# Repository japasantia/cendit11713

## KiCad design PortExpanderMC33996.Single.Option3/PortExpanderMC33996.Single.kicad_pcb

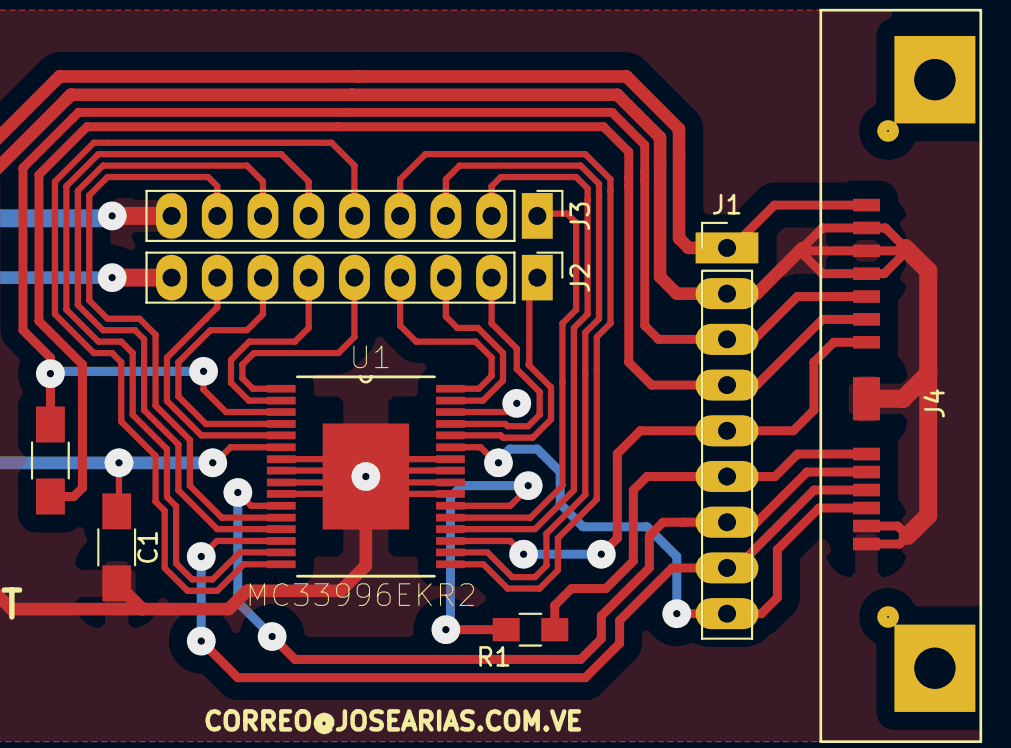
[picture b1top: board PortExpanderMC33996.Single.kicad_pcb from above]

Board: 2 copper layers, 8 parts (0 on the bottom side), 26 nets.

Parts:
C1: 0.1uF/30V; C_1206_HandSoldering
C2: 0.1uF/10V; C_1206_HandSoldering
J1: DEBUG_CON_9P
J2, J3: VIKING_CON_9P; VIKING_HEADER_9P
J4: SATA_CON_14P; SLIMLINE_SATA_PLUG_7P_6P
R1: 1k; R_0805_HandSoldering
U1: MC33996EKR2; MC33996-SOIC32

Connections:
+24.0V: C1.1, J1.1, J2.9, J4.13, U1.6
//CS: J1.8, J4.4, U1.14
//RESET: J1.9, J4.3, U1.27
/MISO: J1.6, J4.6, R1.1
/MOSI: J1.5, J4.7, U1.19
/SCLK: J1.7, J4.5, U1.11
/VKX0: J2.5, U1.1
/VKX1: J2.6, U1.2
/VKX2: J2.7, U1.4
/VKX3: J2.8, U1.5
/VKX4: J3.8, U1.12
/VKX5: J3.7, U1.13
/VKX6: J3.6, U1.15
/VKX7: J3.5, U1.16
/VKX8: J3.4, U1.17
/VKX9: J3.3, U1.18
/VKX10: J3.2, U1.20
/VKX11: J3.1, U1.21
/VKX12: J2.1, U1.28
/VKX13: J2.2, U1.29
/VKX14: J2.3, U1.31
/VKX15: J2.4, U1.32
GND: C2.2, J1.4, J4.8
GNDPWR: C1.2, J1.2, J3.9, J4.1, J4.2, J4.10, J4.11, J4.12, J4.14, U1.7, U1.8, U1.9, U1.10, U1.23, U1.24, U1.25, U1.26, U1.33
unnamed: R1.2, U1.22
VDD: C2.1, J1.3, J4.9, U1.3

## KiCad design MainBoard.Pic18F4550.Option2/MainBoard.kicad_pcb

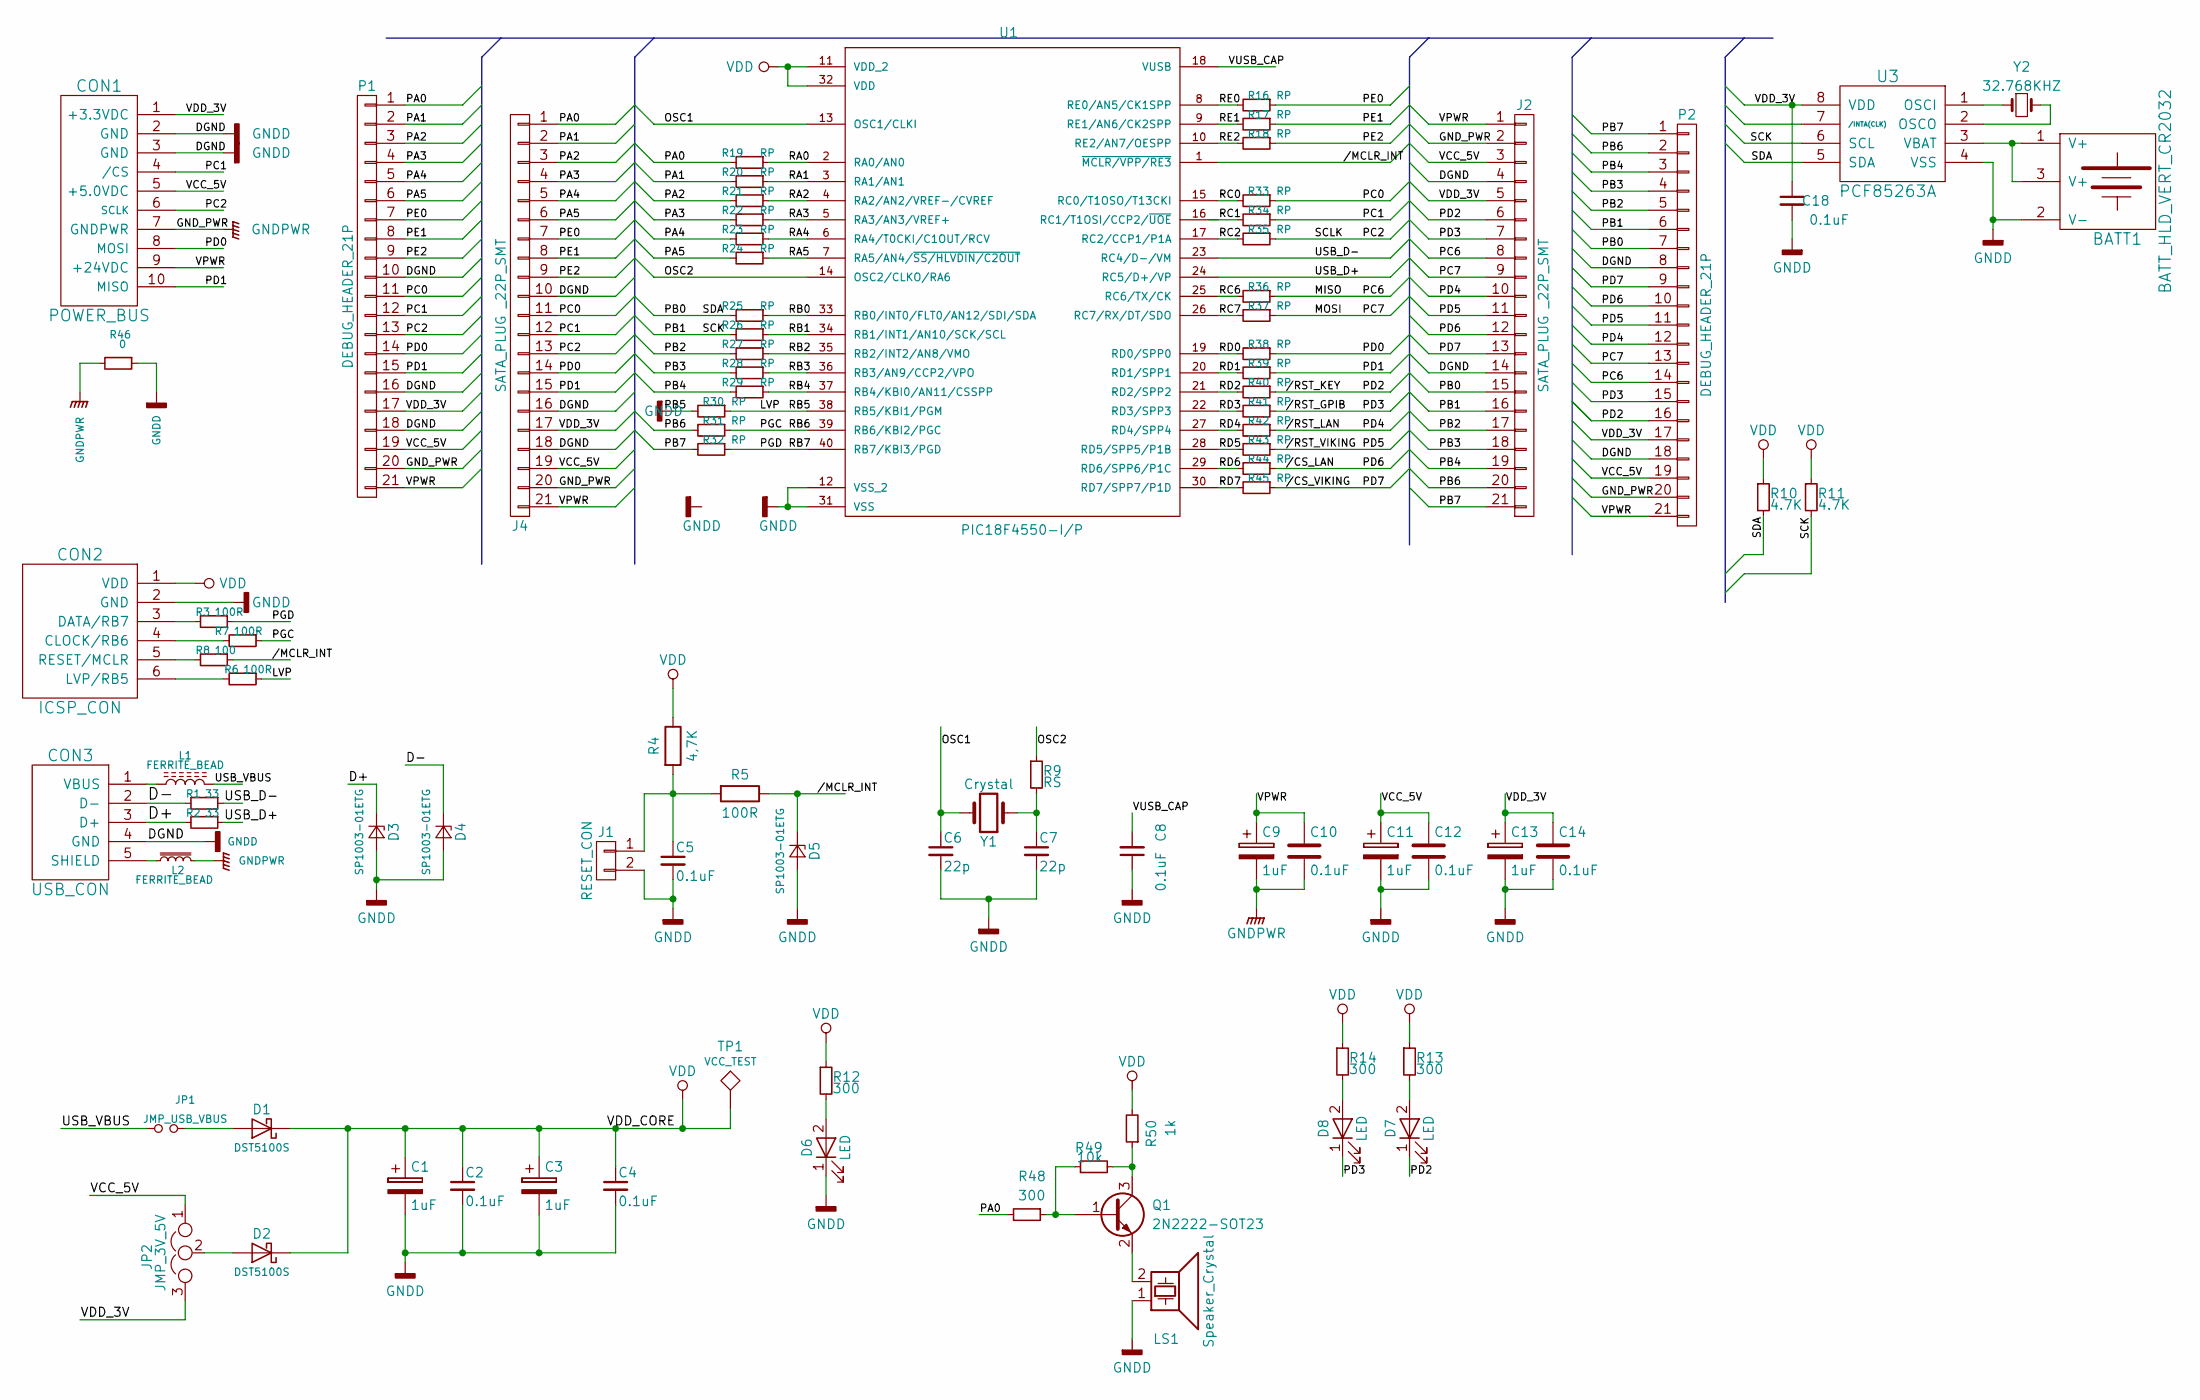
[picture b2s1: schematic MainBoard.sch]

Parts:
BATT1: BATT_HLD_VERT_CR2032; BATTERY_HOLDER_VERT_CR2032
C1, C3, C9, C11, C13: 1uF; C_1206_HandSoldering
C2, C4, C5, C10, C12, C14, C18: 0.1uF; C_0805_HandSoldering
C6, C7: 22p; C_0805_HandSoldering
C8: 0.1uF; C_1206_HandSoldering
CON1: POWER_BUS; Pin_Header_Straight_2x05_Pitch2.54mm
CON2: ICSP_CON; Pin_Header_Straight_2x03
CON3: USB_CON; USB_SMT_B
D1, D2: DST5100S; DST5100S-TO-277B
D3, D4, D5: SP1003-01ETG
D6, D7, D8: LED; LED_0805
J1: RESET_CON; Pin_Header_Straight_1x02_Pitch2.54mm
J2, J4: SATA_PLUG _22P_SMT; SATA_PLUG_22P_SMT
JP1: JMP_USB_VBUS; Pin_Header_Straight_1x02_Pitch2.54mm
JP2: JMP_3V_5V; Pin_Header_Straight_1x03
L1, L2: FERRITE_BEAD; L_Axial_L5.3mm_D2.2mm_P2.54mm_Vertical_Vishay_IM-1
LS1: Speaker_Crystal; MagneticBuzzer_Kingstate_KCG0601
P1, P2: DEBUG_HEADER_21P; DEBUG_PIN_HEADER_21P
Q1: 2N2222-SOT23; SOT-23_Handsoldering
R1, R2: 33; R_0603_HandSoldering
R3, R5, R6, R7: 100R; R_0805_HandSoldering
R4: 4,7K; R_0805_HandSoldering
R8: 100; R_0805_HandSoldering
R9: RS; R_0805_HandSoldering
R10, R11: 4.7K; R_0805_HandSoldering
R12, R13, R14: 300; R_0805_HandSoldering
R16, R17, R18, R19, R20, R21, R22, R23, R24, R25, R26, R27, R28, R29, R30, R31, R32, R33, R34, R35, R36, R37, R38, R39, R40, R41, R42, R43, R44, R45: RP; R_0805_HandSoldering
R46: 0; R_0805_HandSoldering
R48: 300; R_0603_HandSoldering
R49: 10k; R_0603_HandSoldering
R50: 1k; R_0603_HandSoldering
TP1: VCC_TEST
U1: PIC18F4550-I/P; PIC18F4550-PDIP
U3: PCF85263A; PCF85263A_SO8
Y1: Crystal; Crystal_SMD_HC49-SD
Y2: 32.768KHZ; Crystal_C26-LF_d2.1mm_l6.5mm_Vertical

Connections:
//CS_LAN: J2.12, P2.10, R44.1
//CS_VIKING: J2.13, P2.9, R45.1
//MCLR_INT: D5.1 (K), R5.1, R8.1, U1.1 (~MCLR/VPP/RE3)
//RST_GPIB: D8.1 (K), J2.7, P2.15, R41.1
//RST_KEY: D7.1 (K), J2.6, P2.16, R40.1
//RST_LAN: J2.10, P2.12, R42.1
//RST_VIKING: J2.11, P2.11, R43.1
/D+: CON3.3 (D+), D3.1 (K), R2.2
/D-: CON3.2 (D-), D4.1 (K), R1.2
/LVP: R6.1, R30.1, U1.38 (RB5/KBI1/PGM)
/MISO: J2.8, P2.14, R36.1
/MOSI: J2.9, P2.13, R37.1
/OSC1: C6.1, U1.13 (OSC1/CLKI), Y1.2
/OSC2: R9.1, U1.14 (OSC2/CLKO/RA6)
/PA0: J4.1, P1.1, R19.2, R48.2
/PA1: J4.2, P1.2, R20.2
/PA2: J4.3, P1.3, R21.2
/PA3: J4.4, P1.4, R22.2
/PA4: J4.5, P1.5, R23.2
/PA5: J4.6, P1.6, R24.2
/PB0: J2.15, P2.7, R10.2, R25.2, U3.5 (SDA)
/PB1: J2.16, P2.6, R11.2, R26.2, U3.6 (SCL)
/PB2: J2.17, P2.5, R27.2
/PB3: J2.18, P2.4, R28.2
/PB4: J2.19, P2.3, R29.2
/PB6: J2.20, P2.2, R31.2
/PB7: J2.21, P2.1, R32.2
/PC0: J4.11, P1.11, R33.1
/PC1: CON1.4 (/CS), J4.12, P1.12, R34.1
/PC2: CON1.6 (SCLK), J4.13, P1.13, R35.1
/PD0: CON1.8 (MOSI), J4.14, P1.14, R38.1
/PD1: CON1.10 (MISO), J4.15, P1.15, R39.1
/PE0: J4.7, P1.7, R16.1
/PE1: J4.8, P1.8, R17.1
/PE2: J4.9, P1.9, R18.1
/PGC: R7.1, R31.1, U1.39 (RB6/KBI2/PGC)
/PGD: R3.1, R32.1, U1.40 (RB7/KBI3/PGD)
/RA0: R19.1, U1.2 (RA0/AN0)
/RA1: R20.1, U1.3 (RA1/AN1)
/RA2: R21.1, U1.4 (RA2/AN2/VREF-/CVREF)
/RA3: R22.1, U1.5 (RA3/AN3/VREF+)
/RA4: R23.1, U1.6 (RA4/T0CKI/C1OUT/RCV)
/RA5: R24.1, U1.7 (RA5/AN4/~SS/HLVDIN/C2OUT)
/RB0: R25.1, U1.33 (RB0/INT0/FLT0/AN12/SDI/SDA)
/RB1: R26.1, U1.34 (RB1/INT1/AN10/SCK/SCL)
/RB2: R27.1, U1.35 (RB2/INT2/AN8/VMO)
/RB3: R28.1, U1.36 (RB3/AN9/CCP2/VPO)
/RB4: R29.1, U1.37 (RB4/KBI0/AN11/CSSPP)
/RC0: R33.2, U1.15 (RC0/T1OSO/T13CKI)
/RC1: R34.2, U1.16 (RC1/T1OSI/CCP2/~UOE)
/RC2: R35.2, U1.17 (RC2/CCP1/P1A)
/RC6: R36.2, U1.25 (RC6/TX/CK)
/RC7: R37.2, U1.26 (RC7/RX/DT/SDO)
/RD0: R38.2, U1.19 (RD0/SPP0)
/RD1: R39.2, U1.20 (RD1/SPP1)
/RD2: R40.2, U1.21 (RD2/SPP2)
/RD3: R41.2, U1.22 (RD3/SPP3)
/RD4: R42.2, U1.27 (RD4/SPP4)
/RD5: R43.2, U1.28 (RD5/SPP5/P1B)
/RD6: R44.2, U1.29 (RD6/SPP6/P1C)
/RD7: R45.2, U1.30 (RD7/SPP7/P1D)
/RE0: R16.2, U1.8 (RE0/AN5/CK1SPP)
/RE1: R17.2, U1.9 (RE1/AN6/CK2SPP)
/RE2: R18.2, U1.10 (RE2/AN7/OESPP)
/USB_D+: R2.1, U1.24 (RC5/D+/VP)
/USB_D-: R1.1, U1.23 (RC4/D-/VM)
/USB_VBUS: JP1.1, L1.2
/VCC_5V: C11.1, C12.1, CON1.5 (+5.0VDC), J2.3, J4.19, JP2.1, P1.19, P2.19
/VDD_3V: C13.1, C14.1, C18.1, CON1.1 (+3.3VDC), J2.5, J4.17, JP2.3, P1.17, P2.17, U3.8 (VDD)
/VPWR: C9.1, C10.1, CON1.9 (+24VDC), J2.1, J4.21, P1.21, P2.21
/VUSB_CAP: C8.2, U1.18 (VUSB)
GNDD: BATT1.2 (V-), C1.2, C2.2, C3.2, C4.2, C5.2, C6.2, C7.2, C8.1, C11.2, C12.2, C13.2, C14.2, C18.2, CON1.2 (GND), CON1.3 (GND), CON2.2 (GND), CON3.4 (GND), D3.2 (A), D4.2 (A), D5.2 (A), D6.1 (K), J1.2, J2.4, J2.14, J4.10, J4.16, J4.18, LS1.1, P1.10, P1.16, P1.18, P2.8, P2.18, R30.2, R46.1, U1.12 (VSS_2), U1.31 (VSS), U3.4 (VSS)
GNDPWR: C9.2, C10.2, CON1.7 (GNDPWR), J2.2, J4.20, L2.2, P1.20, P2.20, R46.2
unnamed: BATT1.1 (V+), BATT1.3 (V+), U3.3 (VBAT)
unnamed: C5.1, J1.1, R4.2, R5.2
unnamed: C7.1, R9.2, Y1.1
unnamed: CON2.3 (DATA/RB7), R3.2
unnamed: CON2.4 (CLOCK/RB6), R7.2
unnamed: CON2.5 (RESET/MCLR), R8.2
unnamed: CON2.6 (LVP/RB5), R6.2
unnamed: CON3.1 (VBUS), L1.1
unnamed: CON3.5 (SHIELD), L2.1
unnamed: D1.2 (A), JP1.2
unnamed: D2.2 (A), JP2.2
unnamed: D6.2 (A), R12.2
unnamed: D7.2 (A), R13.2
unnamed: D8.2 (A), R14.2
unnamed: LS1.2, Q1.2 (E)
unnamed: Q1.1 (B), R48.1, R49.1
unnamed: Q1.3 (C), R49.2, R50.1
unnamed: U3.1 (OSCI), Y2.1
unnamed: U3.2 (OSCO), Y2.2
VDD: C1.1, C2.1, C3.1, C4.1, CON2.1 (VDD), D1.1 (K), D2.1 (K), R4.1, R10.1, R11.1, R12.1, R13.1, R14.1, R50.2, TP1.1, U1.11 (VDD_2), U1.32 (VDD)

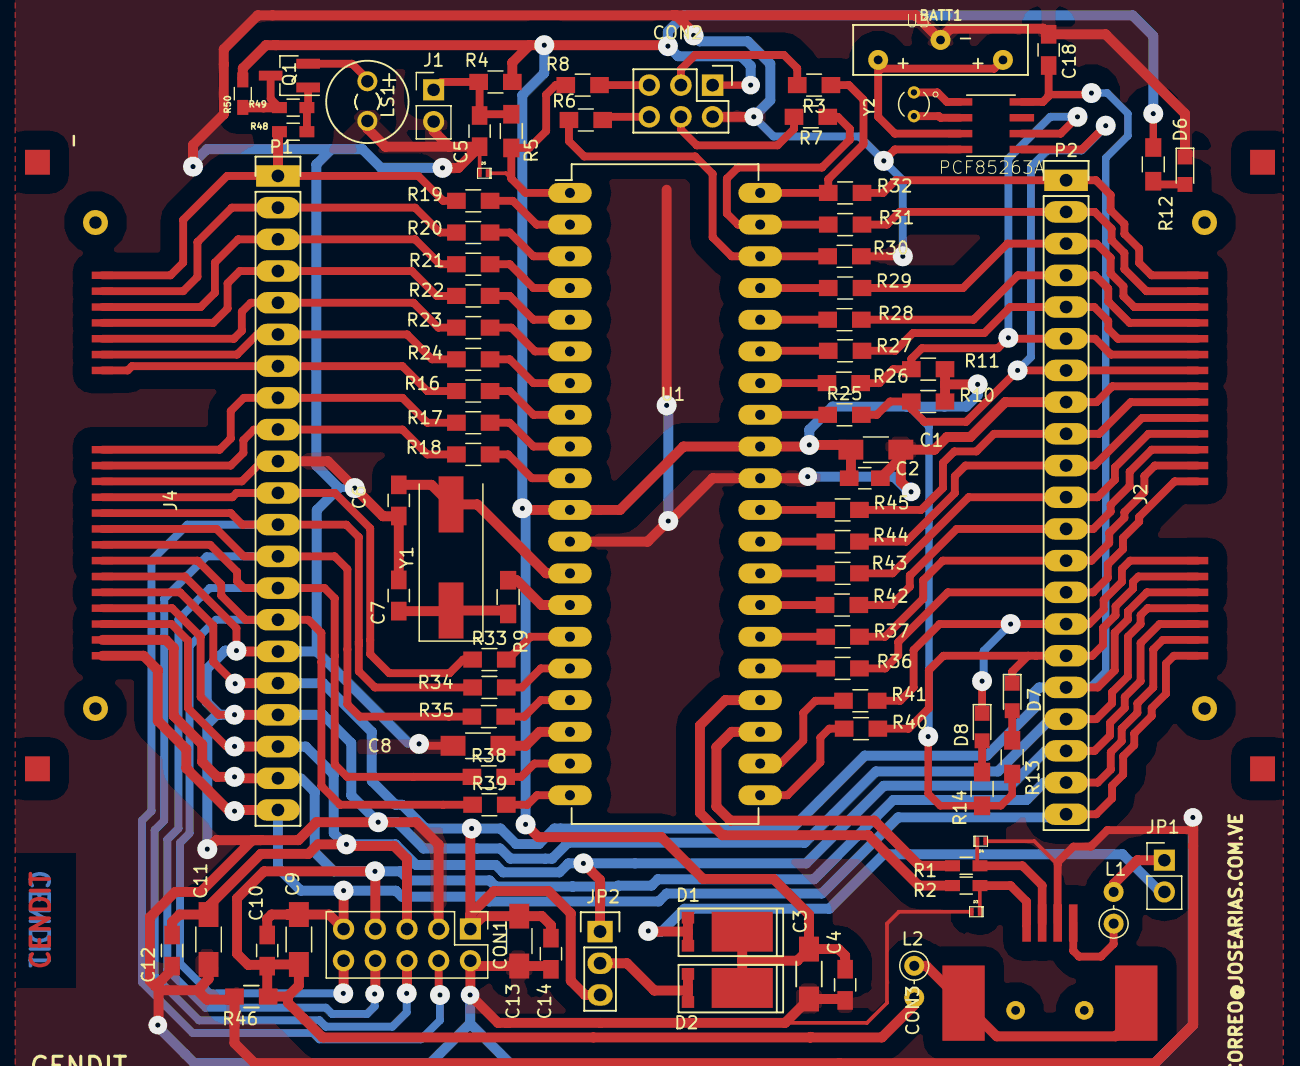
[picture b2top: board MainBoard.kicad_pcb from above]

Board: 2 copper layers, 90 parts (0 on the bottom side), 93 nets.

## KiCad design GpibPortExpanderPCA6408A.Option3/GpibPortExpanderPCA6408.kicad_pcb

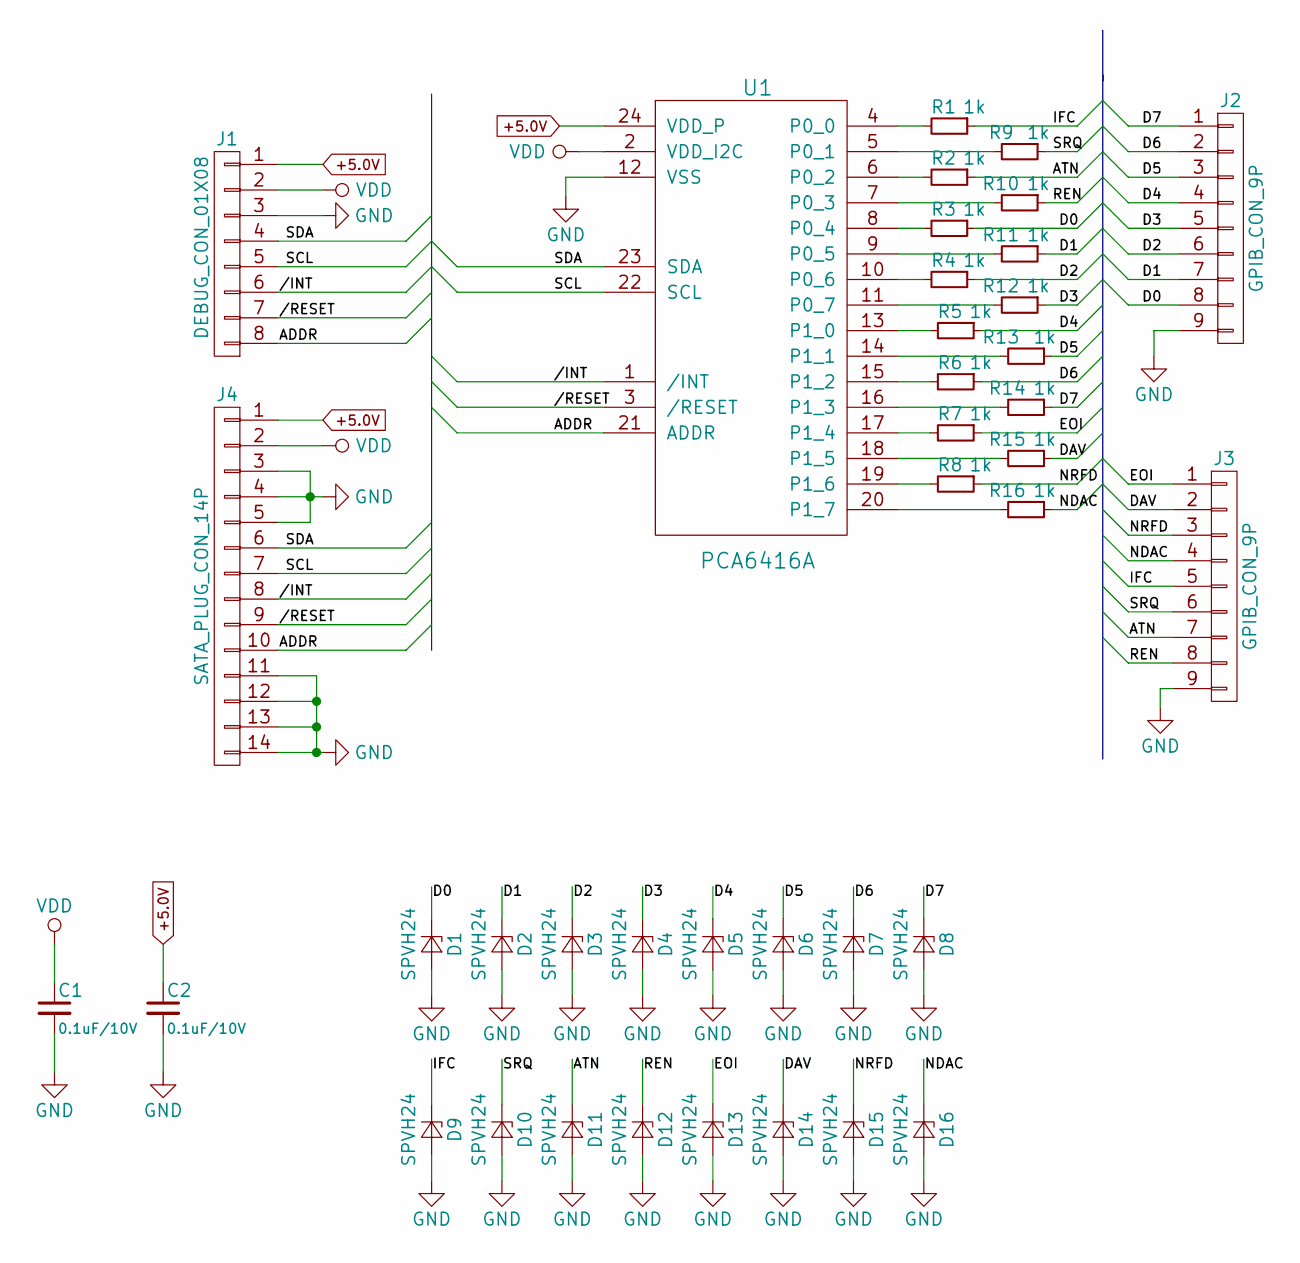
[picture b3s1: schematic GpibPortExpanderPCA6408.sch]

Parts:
C1, C2: 0.1uF/10V; C_1206_HandSoldering
D1, D2, D3, D4, D5, D6, D7, D8, D9, D10, D11, D12, D13, D14, D15, D16: SPVH24; SPHV24-SOD882
J1: DEBUG_CON_01X08; DEBUG_CON_8P
J2, J3: GPIB_CON_9P; GPIB_HEADER_9P
J4: SATA_PLUG_CON_14P; SLIMLINE_SATA_PLUG_7P_6P
R1, R2, R3, R4, R5, R6, R7, R8, R9, R10, R11, R12, R13, R14, R15, R16: 1k; R_0805_HandSoldering
U1: PCA6416A; PCA6416A-TSSOP24

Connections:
+5.0V: C2.1, J1.1, J4.1, U1.24 (VDD_P)
//INT: J1.6, J4.8, U1.1 (/INT)
//RESET: J1.7, J4.9, U1.3 (/RESET)
/ADDR: J1.8, J4.10, U1.21 (ADDR)
/ATN: D11.1 (K), J3.7, R2.1
/D0: D1.1 (K), J2.8, R3.1
/D1: D2.1 (K), J2.7, R11.1
/D2: D3.1 (K), J2.6, R4.1
/D3: D4.1 (K), J2.5, R12.1
/D4: D5.1 (K), J2.4, R5.1
/D5: D6.1 (K), J2.3, R13.1
/D6: D7.1 (K), J2.2, R6.1
/D7: D8.1 (K), J2.1, R14.1
/DAV: D14.1 (K), J3.2, R15.1
/EOI: D13.1 (K), J3.1, R7.1
/IFC: D9.1 (K), J3.5, R1.1
/NDAC: D16.1 (K), J3.4, R16.1
/NRFD: D15.1 (K), J3.3, R8.1
/REN: D12.1 (K), J3.8, R10.1
/SCL: J1.5, J4.7, U1.22 (SCL)
/SDA: J1.4, J4.6, U1.23 (SDA)
/SRQ: D10.1 (K), J3.6, R9.1
GND: C1.2, C2.2, D1.2 (A), D2.2 (A), D3.2 (A), D4.2 (A), D5.2 (A), D6.2 (A), D7.2 (A), D8.2 (A), D9.2 (A), D10.2 (A), D11.2 (A), D12.2 (A), D13.2 (A), D14.2 (A), D15.2 (A), D16.2 (A), J1.3, J2.9, J3.9, J4.3, J4.4, J4.5, J4.11, J4.12, J4.13, J4.14, U1.12 (VSS)
unnamed: R1.2, U1.4 (P0_0)
unnamed: R2.2, U1.6 (P0_2)
unnamed: R3.2, U1.8 (P0_4)
unnamed: R4.2, U1.10 (P0_6)
unnamed: R5.2, U1.13 (P1_0)
unnamed: R6.2, U1.15 (P1_2)
unnamed: R7.2, U1.17 (P1_4)
unnamed: R8.2, U1.19 (P1_6)
unnamed: R9.2, U1.5 (P0_1)
unnamed: R10.2, U1.7 (P0_3)
unnamed: R11.2, U1.9 (P0_5)
unnamed: R12.2, U1.11 (P0_7)
unnamed: R13.2, U1.14 (P1_1)
unnamed: R14.2, U1.16 (P1_3)
unnamed: R15.2, U1.18 (P1_5)
unnamed: R16.2, U1.20 (P1_7)
VDD: C1.1, J1.2, J4.2, U1.2 (VDD_I2C)

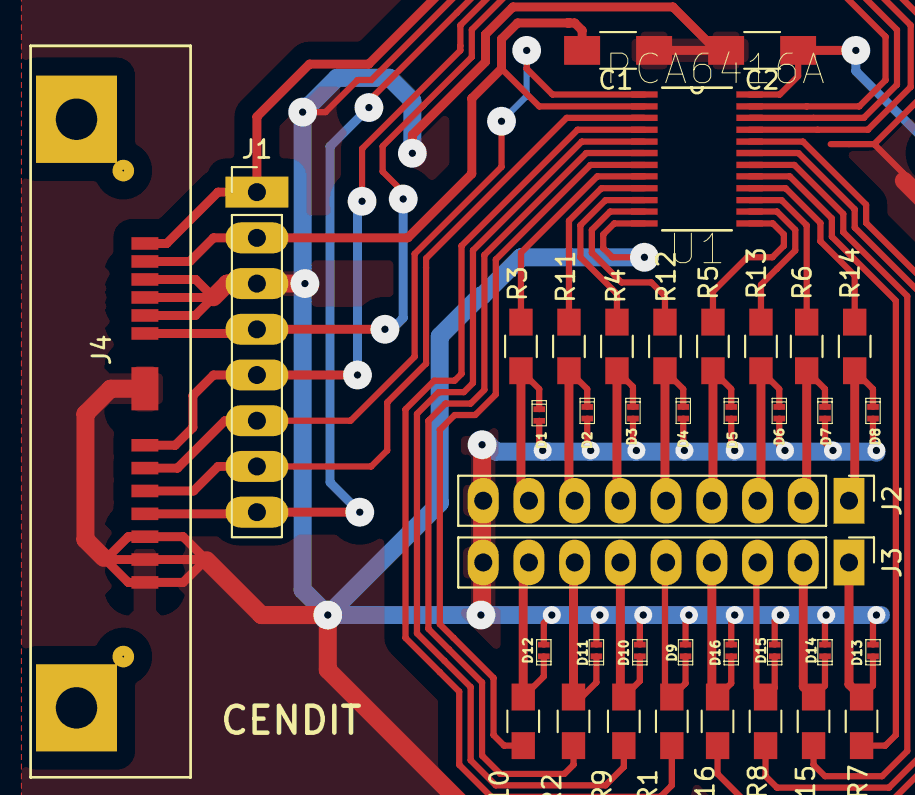
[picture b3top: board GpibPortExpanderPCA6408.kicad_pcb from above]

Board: 2 copper layers, 39 parts (0 on the bottom side), 40 nets.

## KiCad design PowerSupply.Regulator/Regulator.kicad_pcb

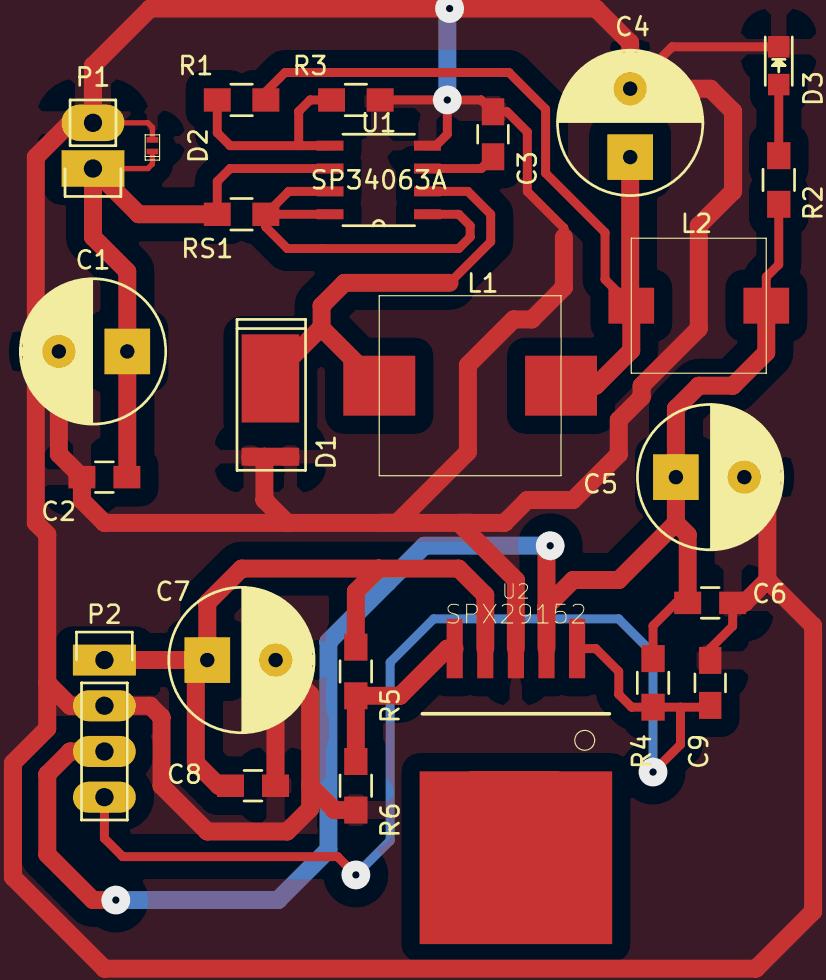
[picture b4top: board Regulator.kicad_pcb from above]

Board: 2 copper layers, 25 parts (0 on the bottom side), 12 nets.

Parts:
C1: 100uF@50V; C_Radial_D8_L13_P3.8
C2, C6, C8: 100nF; C_0805_HandSoldering
C3: 0.3nF; C_0805_HandSoldering
C4: 470uF@10V; C_Radial_D8_L13_P3.8
C5, C7: 100uF@10V; C_Radial_D8_L13_P3.8
C9: 1uF; C_0805_HandSoldering
D1: DST5100S; DST5100S-TO-277B
D2: SPHV24-01ETG; SPHV24-SOD882
D3: LED; LED_0805
L1: 220uH; INDUCTOR_LCM1060
L2: 1uH; INDUCTOR_LKS0745
P1: PWR_IN_2P; Pin_Header_Straight_1x02
P2: PWR_OUT_4P; Pin_Header_Straight_1x04
R1: 2.0k; R_0805_HandSoldering
R2: 330; R_0805_HandSoldering
R3: 1.0k; R_0805_HandSoldering
R4: 10k; R_0805_HandSoldering
R5: 4.3k; R_0805_HandSoldering
R6: 3.0k; R_0805_HandSoldering
RS1: 0.20; R_0805_HandSoldering
U1: SP34063A; SP34063AEN-L&slash_TR
U2: SPX29152; SPX29152T5-TO-263-5

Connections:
/ENABLE: C9.1, P2.4, R4.1, U2.1
GNDPWR: C1.2, C2.2, C3.2, C4.2, C5.2, C6.2, C7.2, C8.2, C9.2, D1.2, D2.2, D3.1, P1.2, P2.2, R3.1, R6.1, U1.4, U2.3
unnamed: C3.1, U1.3
unnamed: C4.1, L1.2, L2.1, R1.1
unnamed: D1.1, L1.1, U1.2
unnamed: D3.2, R2.2
unnamed: R1.2, R3.2, U1.5
unnamed: R5.1, R6.2, U2.5
unnamed: RS1.1, U1.1, U1.7, U1.8
VIN: C1.1, C2.1, D2.1, P1.1, RS1.2, U1.6
VOUT: C7.1, C8.1, P2.1, R5.2, U2.4
VREG: C5.1, C6.1, L2.2, P2.3, R2.1, R4.2, U2.2

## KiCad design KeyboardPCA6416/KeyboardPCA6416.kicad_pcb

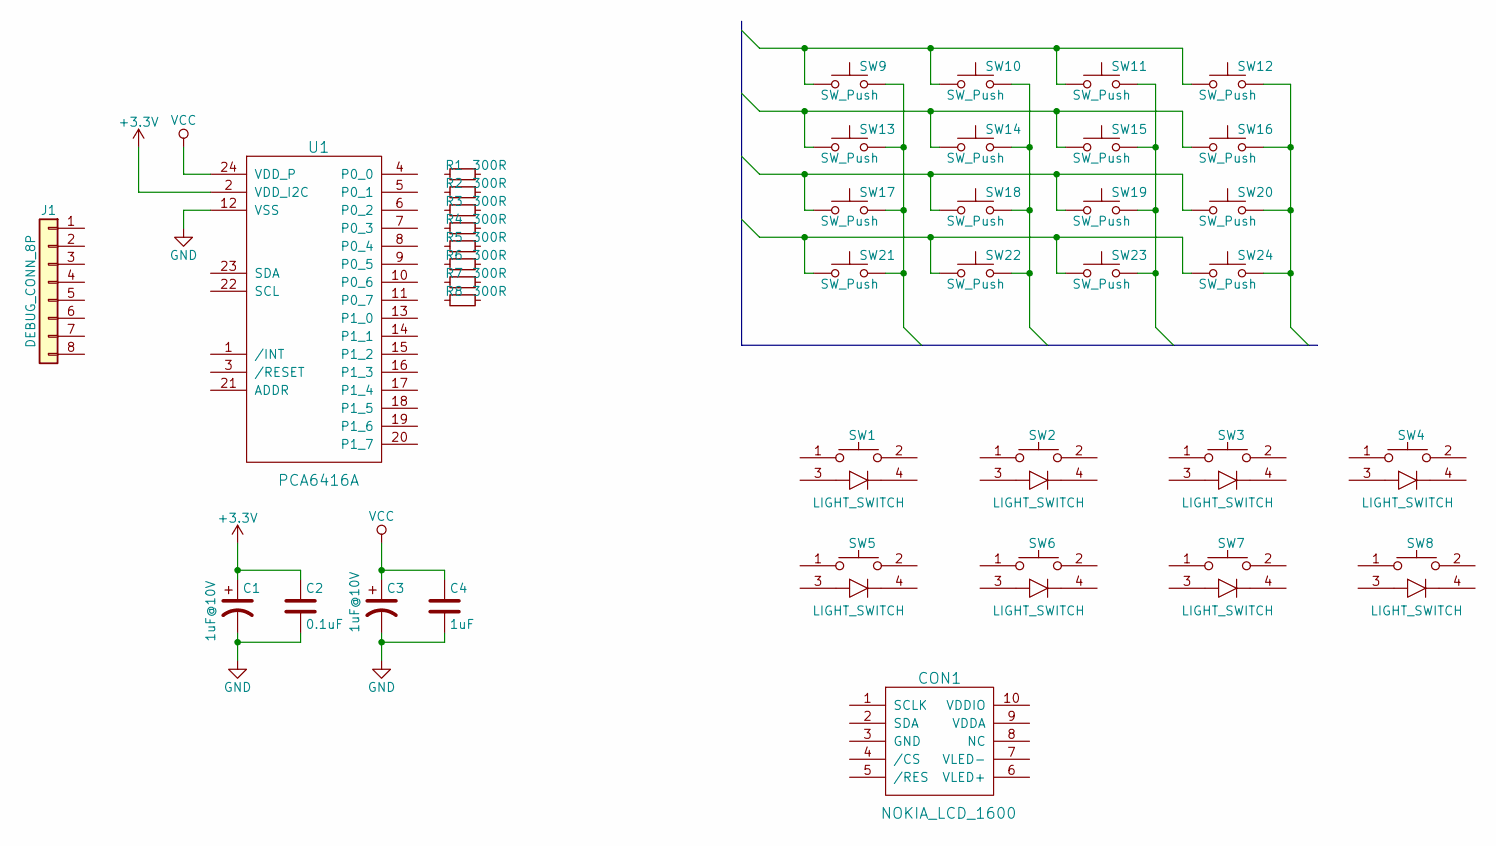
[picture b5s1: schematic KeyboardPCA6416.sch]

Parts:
C1, C3: 1uF@10V; C_0805_HandSoldering
C2: 0.1uF; C_0805_HandSoldering
C4: 1uF; C_0805_HandSoldering
CON1: NOKIA_LCD_1600; HIROSE_DF23C_10P
J1: DEBUG_CONN_8P; Pin_Header_Straight_1x08_Pitch2.54mm
R1, R2, R3, R4, R5, R6, R7, R8: 300R; R_0805_HandSoldering
SW1, SW2, SW3, SW4, SW5, SW6, SW7, SW8: LIGHT_SWITCH; LIGHT_SWITCH_THT
SW9, SW10, SW11, SW12, SW13, SW14, SW15, SW16, SW17, SW18, SW19, SW20, SW21, SW22, SW23, SW24: SW_Push; SWITCH_THT_6MM
U1: PCA6416A; PCA6416A-TSSOP24

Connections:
+3V3: C1.1, C2.1, U1.2 (VDD_I2C)
GND: C1.2, C2.2, C3.2, C4.2, U1.12 (VSS)
unnamed: SW9.1, SW10.1, SW11.1, SW12.1
unnamed: SW10.2, SW14.2, SW18.2, SW22.2
unnamed: SW11.2, SW15.2, SW19.2, SW23.2
unnamed: SW12.2, SW16.2, SW20.2, SW24.2
unnamed: SW13.1, SW14.1, SW15.1, SW16.1
unnamed: SW9.2, SW13.2, SW17.2, SW21.2
unnamed: SW17.1, SW18.1, SW19.1, SW20.1
unnamed: SW21.1, SW22.1, SW23.1, SW24.1
VCC: C3.1, C4.1, U1.24 (VDD_P)

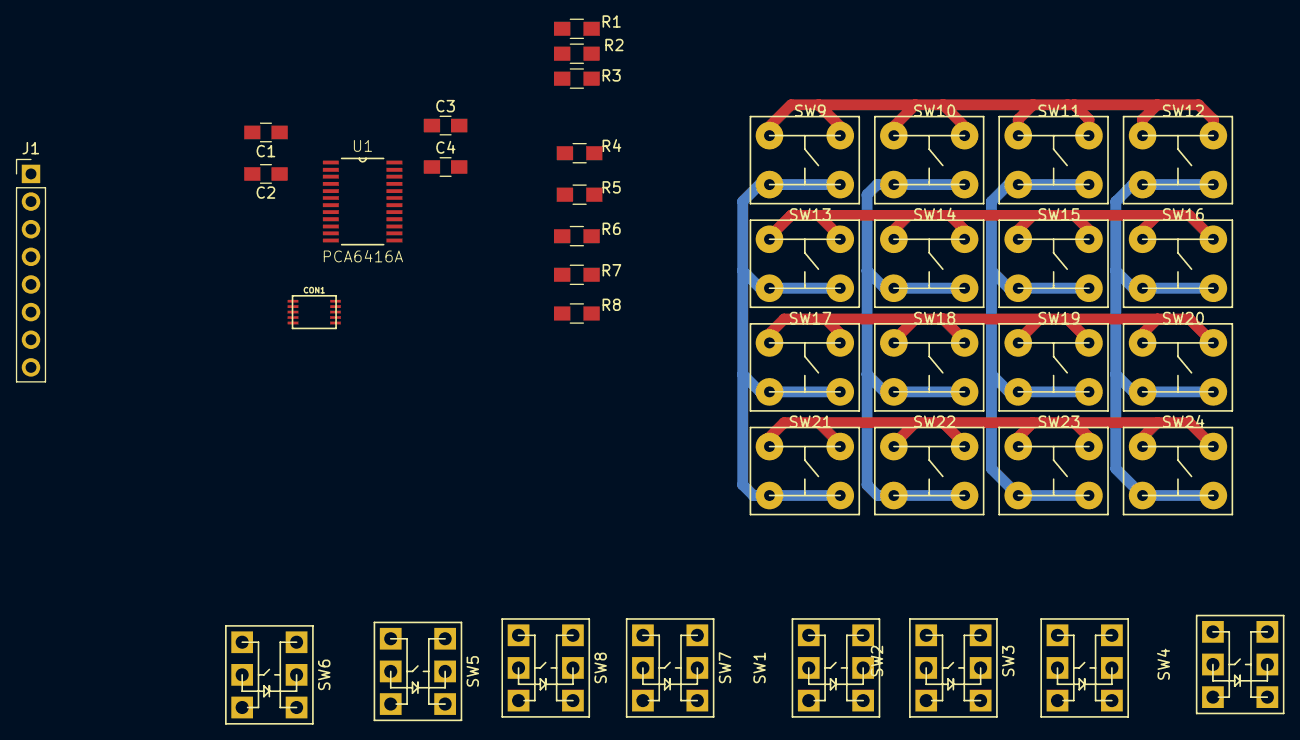
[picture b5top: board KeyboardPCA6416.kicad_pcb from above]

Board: 2 copper layers, 39 parts (0 on the bottom side), 11 nets.

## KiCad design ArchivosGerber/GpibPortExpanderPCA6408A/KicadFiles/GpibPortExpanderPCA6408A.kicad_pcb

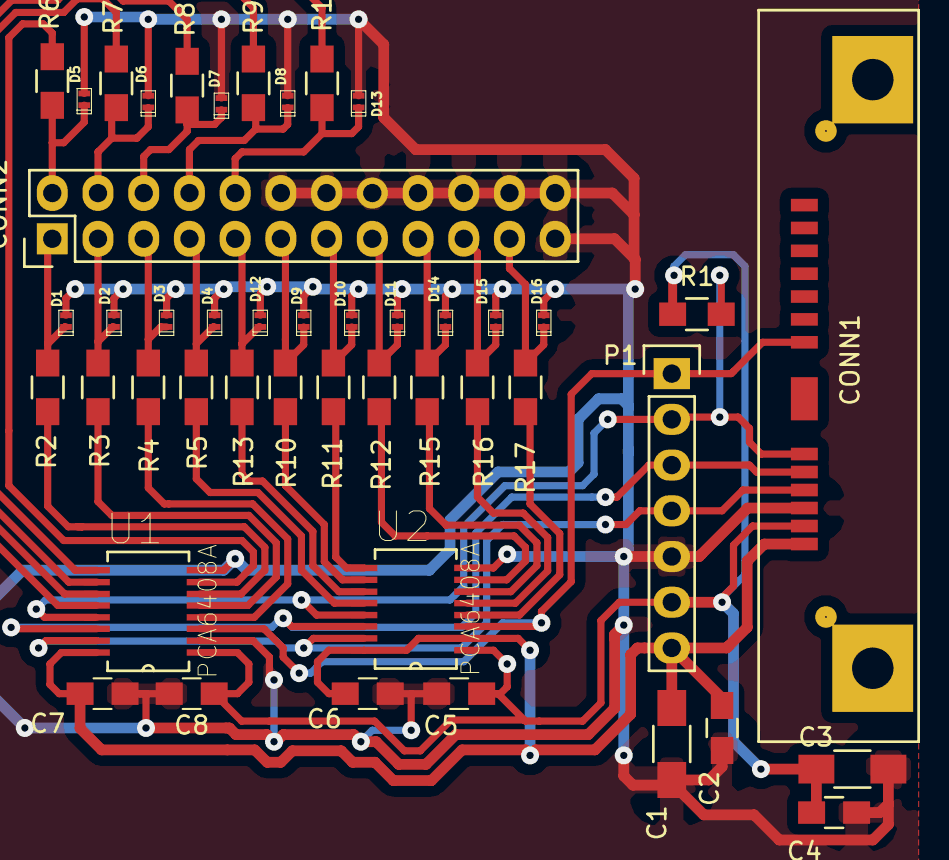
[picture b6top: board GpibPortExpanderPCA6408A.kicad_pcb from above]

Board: 2 copper layers, 46 parts (0 on the bottom side), 39 nets.

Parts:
C1, C3: 1uF; C_1206_HandSoldering
C2, C4, C5, C6, C7, C8: 0.1uF; C_0805_HandSoldering
CONN1: I2C_BUS; SLIMLINE_SATA_PLUG_7P_6P
CONN2: GPIB_CONN; GPIB_HEADER_12X2P
D1, D2, D3, D4, D5, D6, D7, D8, D9, D10, D11, D12, D13, D14, D15, D16: SPHV24; SPHV24-SOD882
P1: CONN_01X07; Pin_Header_Straight_1x07
R1: R; R_0805_HandSoldering
R2, R3, R4, R5, R6, R7, R8, R9, R10, R11, R12, R13, R14, R15, R16, R17: RB; R_0805_HandSoldering
U1, U2: PCA6408A; PCA6408A-SOP16

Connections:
+3V3: C3.1, C4.1, C6.1, C8.1, CONN1.2, P1.6, R1.1, U1.1, U2.1
+5V: C1.1, C2.1, C5.1, C7.1, CONN1.1, P1.7, U1.16, U2.2, U2.16
//INT: CONN1.6, P1.2, R1.2, U1.13, U2.13
//RESET: CONN1.7, P1.1, U1.3, U2.3
/ATN: CONN2.21, D16.1, R17.1
/D0: CONN2.1, D1.1, R2.1
/D1: CONN2.3, D2.1, R3.1
/D2: CONN2.5, D3.1, R4.1
/D3: CONN2.7, D4.1, R5.1
/D4: CONN2.2, D5.1, R6.1
/D5: CONN2.4, D6.1, R7.1
/D6: CONN2.6, D7.1, R8.1
/D7: CONN2.8, D8.1, R9.1
/DAV: CONN2.11, D9.1, R10.1
/EOI: CONN2.9, D12.1, R13.1
/IFC: CONN2.17, D14.1, R15.1
/NDAC: CONN2.15, D11.1, R12.1
/NRFD: CONN2.13, D10.1, R11.1
/PATN: R17.2, U2.4
/PD0: R2.2, U1.6
/PD1: R3.2, U1.5
/PD2: R4.2, U1.4
/PD3: R5.2, U2.12
/PD4: R6.2, U1.7
/PD5: R7.2, U1.9
/PD6: R8.2, U1.10
/PD7: R9.2, U1.11
/PDAV: R12.2, U2.7
/PEOI: R13.2, U2.11
/PIFC: R15.2, U2.6
/PNDAC: R10.2, U2.10
/PNRFD: R11.2, U2.9
/PREN: R14.2, U1.12
/PSRQ: R16.2, U2.5
/REN: CONN2.10, D13.1, R14.1
/SCL: CONN1.5, P1.3, U1.14, U2.14
/SDA: CONN1.4, P1.4, U1.15, U2.15
/SRQ: CONN2.19, D15.1, R16.1
GNDD: C1.2, C2.2, C3.2, C4.2, C5.2, C6.2, C7.2, C8.2, CONN1.3, CONN2.12, CONN2.14, CONN2.16, CONN2.18, CONN2.20, CONN2.22, CONN2.23, CONN2.24, D1.2, D2.2, D3.2, D4.2, D5.2, D6.2, D7.2, D8.2, D9.2, D10.2, D11.2, D12.2, D13.2, D14.2, D15.2, D16.2, P1.5, U1.2, U1.8, U2.8

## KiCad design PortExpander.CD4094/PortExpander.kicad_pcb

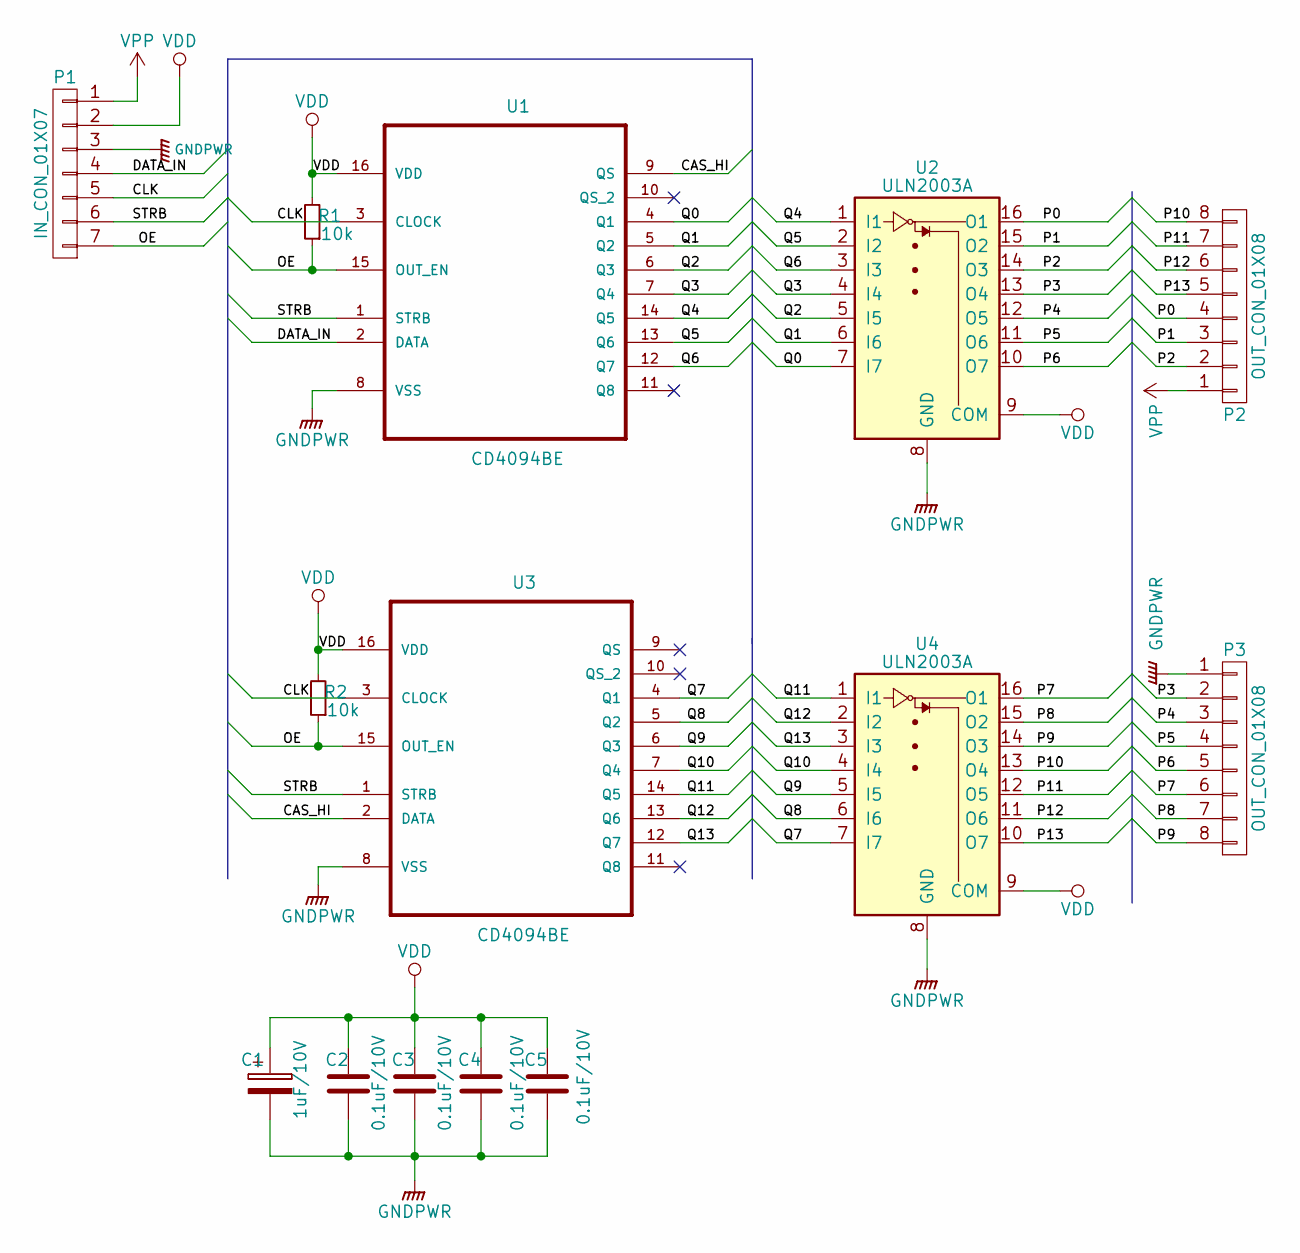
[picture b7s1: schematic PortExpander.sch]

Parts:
C1: 1uF/10V; C_0805_HandSoldering
C2, C3, C4, C5: 0.1uF/10V; C_0805_HandSoldering
P1: IN_CON_01X07; Pin_Header_Straight_1x07_Pitch2.54mm
P2, P3: OUT_CON_01X08; Pin_Header_Straight_1x08_Pitch2.54mm
R1, R2: 10k; R_0805_HandSoldering
U1, U3: CD4094BE; CD4094-DIP16
U2, U4: ULN2003A; ULN2003-DIP16

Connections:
/CAS_HI: U1.9 (QS), U3.2 (DATA)
/CLK: P1.5, U1.3 (CLOCK), U3.3 (CLOCK)
/DATA_IN: P1.4, U1.2 (DATA)
/OE: P1.7, R1.1, R2.1, U1.15 (OUT_EN), U3.15 (OUT_EN)
/P0: P2.4, U2.16 (O1)
/P1: P2.3, U2.15 (O2)
/P2: P2.2, U2.14 (O3)
/P3: P3.2, U2.13 (O4)
/P4: P3.3, U2.12 (O5)
/P5: P3.4, U2.11 (O6)
/P6: P3.5, U2.10 (O7)
/P7: P3.6, U4.16 (O1)
/P8: P3.7, U4.15 (O2)
/P9: P3.8, U4.14 (O3)
/P10: P2.8, U4.13 (O4)
/P11: P2.7, U4.12 (O5)
/P12: P2.6, U4.11 (O6)
/P13: P2.5, U4.10 (O7)
/Q0: U1.4 (Q1), U2.7 (I7)
/Q1: U1.5 (Q2), U2.6 (I6)
/Q2: U1.6 (Q3), U2.5 (I5)
/Q3: U1.7 (Q4), U2.4 (I4)
/Q4: U1.14 (Q5), U2.1 (I1)
/Q5: U1.13 (Q6), U2.2 (I2)
/Q6: U1.12 (Q7), U2.3 (I3)
/Q7: U3.4 (Q1), U4.7 (I7)
/Q8: U3.5 (Q2), U4.6 (I6)
/Q9: U3.6 (Q3), U4.5 (I5)
/Q10: U3.7 (Q4), U4.4 (I4)
/Q11: U3.14 (Q5), U4.1 (I1)
/Q12: U3.13 (Q6), U4.2 (I2)
/Q13: U3.12 (Q7), U4.3 (I3)
/STRB: P1.6, U1.1 (STRB), U3.1 (STRB)
GNDPWR: C1.2, C2.2, C3.2, C4.2, C5.2, P1.3, P3.1, U1.8 (VSS), U2.8 (GND), U3.8 (VSS), U4.8 (GND)
VDD: C1.1, C2.1, C3.1, C4.1, C5.1, P1.2, R1.2, R2.2, U1.16 (VDD), U2.9 (COM), U3.16 (VDD), U4.9 (COM)
VPP: P1.1, P2.1

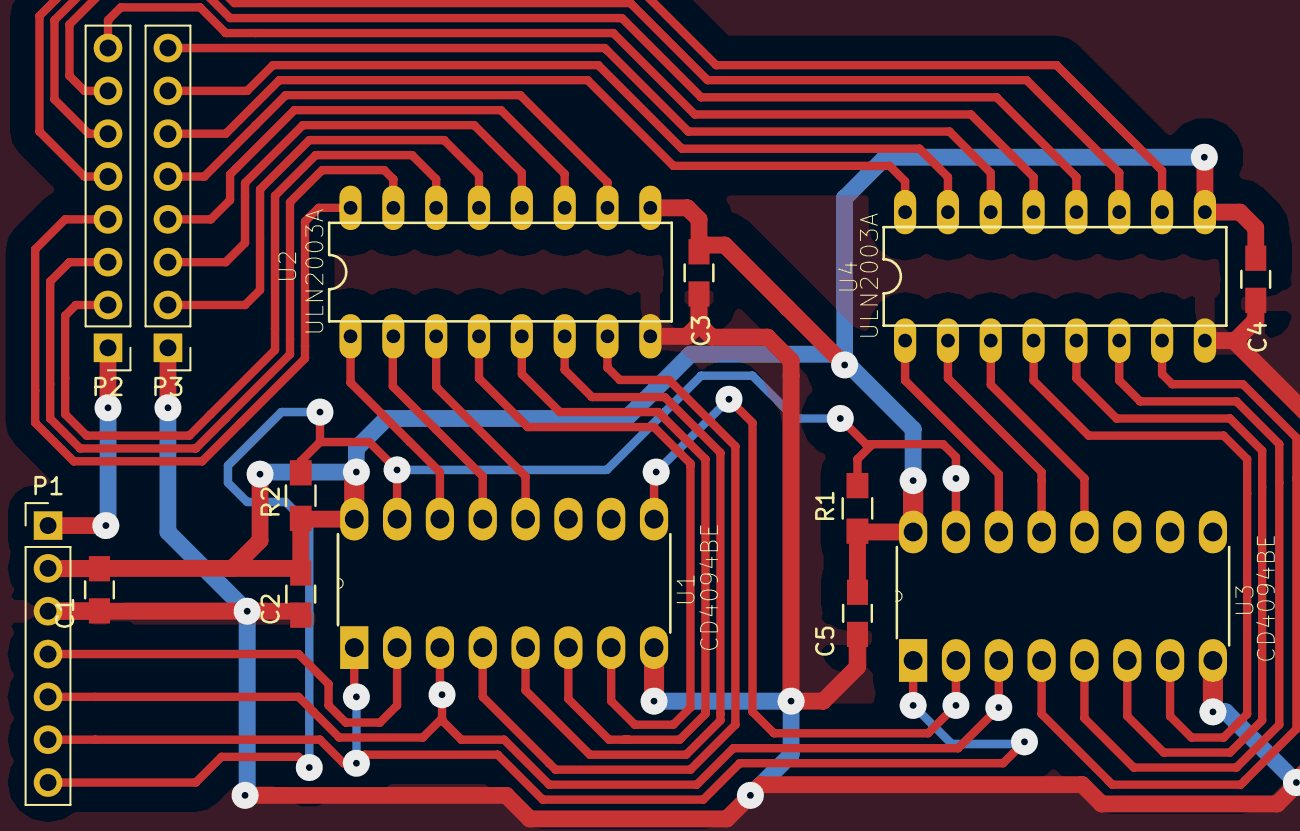
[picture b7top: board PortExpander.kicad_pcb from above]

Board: 2 copper layers, 14 parts (0 on the bottom side), 36 nets.

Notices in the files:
parts and their libraries:
Copyright 2016 Accelerated Designs. All rights reserved.
